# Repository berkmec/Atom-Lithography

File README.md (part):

# Atom Litografi Makinesi (v7.2)

TRL 1–2 (`M0`) Kavramsal Sistem Tasarımı, İndirgenmiş-Mertebe Çok-Fizikli Fizibilite Çalışması, Gerçek-EDA Doğrulamalı Verilog RTL ve Bulut Süperiletken-QPU Kontrol/Dekoder Kıyaslaması

Doğrudan Artefaktlar: [**180/180 Parça Mühendislik Planı (`hardware/DESIGN_BLUEPRINT_180_SUMMARY.md`)**](hardware/DESIGN_BLUEPRINT_180_SUMMARY.md) · [**164-Parça Ana Montaj Paftası (`hardware/cad_parts/master_164_assembly_views.png`)**](hardware/cad_parts/master_164_assembly_views.png) · [Makine-Kontrol RTL (`rtl/machine_ctrl/README.md`)](rtl/machine_ctrl/README.md) · [Etkileşimli HTML5 Model Gezgini (`docs/digital_twin_interactive.html`)](docs/digital_twin_interactive.html) · [BOED Verilog RTL (`rtl/boed_fpga/README.md`)](rtl/boed_fpga/README.md) · [Ana Tasarım (`DESIGN.md`)](research/atom_lithography_machine/DESIGN.md) · [Teknik El Kitabı (`TECHNICAL_MANUAL.md`)](research/atom_lithography_machine/TECHNICAL_MANUAL.md)

---

## Özet

Atom Litografi Makinesi (`v7.2`), zenginleştirilmiş `²⁸Si` üzerinde deterministik tek-atom donör yerleşimi ve hata-toleranslı ölçekleme için geliştirilmiş **`TRL 1–2` (`M0/M1 DESIGN_ONLY`) düzeyinde kavramsal bir sistem mimarisi ve indirgenmiş-mertebe çok-fizikli fizibilite çalışmasıdır**. Depo, `28` ön-kayıtlı sayısal çalışmayı (`Exp124`–`Exp151`), konak makinede gerçek açık-kaynak EDA araçlarıyla (`iverilog 14.0`, `verilator 5.055`, `yosys 0.71+101`, `nextpnr-ecp5` vekili; `no_external_eda_sim = false`, `no_vendor_vivado_pnr = true`, `no_lab_measurement_rtl = true`) doğrulanmış sentezlenebilir IEEE 1364-2005 `Q16.16` BOED-FPGA ve makine-kontrol Verilog RTL modüllerini (`rtl/boed_fpga/`, `rtl/machine_ctrl/`, `rtl/cryo_crossbar_4k/`), gerçek `1% ²⁹Si` elmas-kübik örgü banyosu BOED kıyaslamasını (`results/boed_real_bath_benchmark.json`: `130,4 ms/aday`, `%91,15` doğruluk), fiziksel ODE/PDE/Lindblad/GF(2) tabanlı `auto_recal.py` ve `programmer.py` çözücülerini, `SEMI S2` kılavuzları ve `IEC 61508 SIL-3` mimari hedeflerini referans alan sertifikasız bir `M0` ön emniyet FMEA/HAZOP taramasını (`iec61508_certified = false`, `semi_s2_certified = false`, IEC 61508-6 `PFH` ve `15`-durumlu `λ_DU × β` duyarlılık taraması, `12,0 kWh` LFP UPS `202,8 dk @ %90 DoD`), **tek birleştirilmiş `164` fiziksel katı parçalık su-sızdırmaz 3B CAD ana montajını (`2.957,95 kg`, `0 / 13.366` çakışma, `32/32` kriyo termal, `10/10` GD&T; `10/10` KiCad 8 PCB `1.128/1.128` ağ `0` ERC/`0` DRC + `ngspice-47`)** ve `180` satırlık parametrik `BOM v7.0` (`10-RFQ` taslağı, `no_supplier_quotes = true`, `1.392/1.392` `%100` `SHA-256` sabitli `hardware/parts_registry.json`) paketini birleştirir. Seçili alt-çözücüler mikroskobik veya cebirsel denklemleri doğrudan çözerken sistem düzeyindeki proses, QEC (Stim devre eşiği `%0,60–%0,98`; `Exp147` `FeMoco d=18` ve `RSA-2048 d=24` `p_fail_total = 1,0`, `RSA-2048 d_req = 174,1`), emniyet, maliyet ve kapasite kestirimleri **parametrik/indirgenmiş-mertebe modellere ve literatür varsayımlarına** dayanır. Ayrıca `CellISA v4.0 → OpenQASM 3.0` kontrol derleyicisi, dinamik dekupling, `d=3` tekrar dekoderi ve bit-kesin `Q16.16` BOED algoritmaları `156`-kübitlik süperiletken `ibm_marrakesh` bulut QPU işlemcisinde kontrol/dekoder proxy kıyaslaması olarak çalıştırılmıştır (`Exp145`; silikon fabrikasyonunu doğrulamaz).

## Abstract

Atom Lithography Machine (`v7.2`) is a **`TRL 1–2` (`M0/M1 DESIGN_ONLY`) conceptual systems-architecture and reduced-order multiphysics feasibility study** for deterministic single-atom donor placement in enriched `²⁸Si` and fault-tolerant quantum scaling. The repository combines `28` preregistered numerical studies (`Exp124`–`Exp151`), synthesizable IEEE 1364-2005 `Q16.16` BOED-FPGA and machine-control Verilog RTL verified with real open-source EDA tools on host (`iverilog 14.0`, `verilator 5.055`, `yosys 0.71+101`, `nextpnr-ecp5` proxy; `no_external_eda_sim = false`, `no_vendor_vivado_pnr = true`, `no_lab_measurement_rtl = true`), a real `1% ²⁹Si` diamond-cubic lattice-bath BOED benchmark (`results/boed_real_bath_benchmark.json`: `130.4 ms/cand`, `91.15%` accuracy), physics-based ODE/PDE/Lindblad/GF(2) solvers in `auto_recal.py` and `programmer.py`, an uncertified `M0` preliminary parametric safety FMEA/HAZOP screening (`iec61508_certified = false`, `semi_s2_certified = false`, IEC 61508-6 PFH & `15`-case `λ_DU × β` sweep, upgraded `12.0 kWh` LFP UPS `202.8 min @ 90% DoD`), a **single reconciled `164`-part watertight 3D engineering CAD assembly (`2,957.95 kg`, `0 / 13,366` 3D solid clashes, `32/32` NIST cryo thermal checks, `10/10` GD&T stacks; `10/10` KiCad 8 PCBs `1,128/1,128` nets `0` ERC/`0` DRC + live `ngspice-47`)**, and a parametric `180`-row `BOM v7.0` (`10-RFQ` draft, `no_supplier_quotes = true`, `1,392/1,392` `100%` SHA-256 pinned in `hardware/parts_registry.json`). While selected sub-solvers evaluate microscopic or algebraic physics, system-level process, QEC (honest Stim circuit threshold `0.60–0.98%`; `Exp147` `FeMoco d=18` and `RSA-2048 d=24` yield `p_fail_total = 1.0` under D3 with `RSA-2048 d_req = 174.1`), safety, cost, and throughput estimates rely on **parametric/reduced-order models and literature assumptions**. Separately, the `CellISA v4.0 → OpenQASM 3.0` compiler, dynamical decoupling, `d=3` repetition decoding, and bit-exact `Q16.16` BOED routines were executed on the `156`-qubit superconducting `ibm_marrakesh` cloud QPU as a non-silicon control/decoder proxy (`Exp145`).

---

## Bu Depo Neyi Gösterir, Neyi Kanıtlamaz? (Scope: Demonstrated vs. Not Demonstrated)

| Alan | Gösterilen (Demonstrated) | Kanıtlanmayan (Not Demonstrated) |
|---|---|---|
| Bulut QPU (`Exp145`, `ibm_marrakesh`) | `CellISA v4.0 → OpenQASM 3.0` derleyici, `Echo / XY4`, `d=3` tekrar dekoderi ve `Q16.16` BOED algoritmalarının süperiletken transmon bulut işlemcisinde (`job_id = dc1tdo2nj2vs73dfrfl0`) çalıştırıldığını gösterir. | Silikon `³¹P` implantasyonu, flaş tavlama, MBE, `100 K` IBIC veya herhangi bir atom-litografi donanımını doğrulamaz. |
| Gerçek Açık-Kaynak EDA RTL & ASIC Durumu (`Exp149`, `rtl/boed_fpga/`, `rtl/machine_ctrl/`, `S8.2-02`) | `verilator 5.055 --lint-only -Wall` (`0` uyarı/hata), `iverilog 14.0 + vvp` (`64/64` vektör + `4`-kanal AXI4-Stream `0 LSB`, `584` çevrim, `0` kombinasyonel `/`), `yosys 0.71+101` (`xcup`/`xc7`/`ecp5`) ve `nextpnr-ecp5` (`LFE5U-85F` vekili: `boed_q16_core 43,58 MHz`, `fpga_top_carrier_wrap 79/205 TRELLIS_IO`); `no_external_eda_sim = false`, `real_eda_verified = true`. | Ticari Xilinx Vivado `ZU48DR`/`XC7K325T` P&R zamanlama kapanışı (`no_vendor_vivado_pnr = true`), fiziksel FPGA ölçümü (`no_lab_measurement_rtl = true`) ve SKY130 ASIC tape-out (`tapeout_done = false`, `PRE_FOUNDRY_NCH8_MACRO_PROTOTYPE_NOT_TAPEOUT_READY`, `Exp123 Attempt-2` geçersiz) henüz yapılmamıştır. |
| Yazılım Regresyon Testleri (**`621/621`** çıplak `pytest`, **`50`** takip edilen test dosyası) | Kod tabanının yeniden üretilebilirliğini, birim doğruluğunu, açık-kaynak EDA eş-doğrulamasını ve iç sayısal tutarlılığını gösterir (`35` v7.2 + `14` Stage-2 + `1` `test_qcell_legacy.py` = `50` takip edilen suit; çıplak `pytest -q`: `621 passed, 0 failed`, yeniden koşumda `0` dosya değişimi). | Fiziksel modelin gerçek laboratuvar koşullarında doğru olduğunu kanıtlamaz. |
| Dosya Bütünlüğü (`39/39` v7.2 + `1.392/1.392` Stage-2 `%100` `SHA-256`) | Üretilen artefaktların sonradan değiştirilmediğini doğrulayan dosya-bütünlüğü ve izlenebilirlik özetidir (`hardware/parts_registry.json`, `180/180` boş-olmayan ICD `verification_tests`). | Bilimsel doğrulama, hakemli onay veya endüstriyel sertifikasyon değildir. |
| Fizik, QEC (`Stim`/`Exp147`), `1% ²⁹Si` Banyo & Maliyet (`Exp124`–`Exp151`) | Atomistik/cebirsel hesabı (`sp³d⁵s*` TB, `16B` Lindblad + Gillespie-OU, `45.214` konumlu `1% ²⁹Si` banyo [`130,4 ms/aday`], Stim devre eşiği `%0,60–%0,98`, GF(2) BP-OSD, doğrusal-olmayan Si PDE, UHV ODE) sistem düzeyinde parametrik analizle birleştirir; tüm ön-kayıtlı `FAIL` ve fiziksel duvarları (`Exp147` `UQ4/UQ5/UQ6 FAIL`: `FeMoco d=18` & `RSA-2048 d=24` `p_fail_total = 1,0`, `RSA-2048 d_req = 174,1`; `CPU ldpc BP+OSD-2 34,7–181,7 ms`, sıfır QEC dekoder RTL; `2 kHz` Fourier duvarı; `SNR ≤ 3` uçurumu; `%61,51` step-and-stitch) korur. | Uçtan uca deneysel fiziksel doğrulama veya tedarikçi teklifi değildir (`no_lab_measurement = true`, `no_supplier_quotes = true`, `tapeout_done = false`). |
| Emniyet Analizi (`Exp150`, `PRELIMINARY_PARAMETRIC_CALCULATION_NOT_CERTIFIED`) | `25` satırlı ön `M0` tehlike taraması (`FMEA`), `10` düğümlü `HAZOP`, IEC 61508-6 `PFH` & `15`-durumlu `1oo2D` `λ_DU × β` duyarlılık taraması, RK4 oda ODH geçişi (`60 m³ 0 ACH = %20,57`; havalandırmasız `≤15 m³` oda `%19,47 < %19,5` yasak), yükseltilmiş `12,0 kWh` LFP UPS (`202,8 dk @ %90 DoD ≥ 180 dk`) ve `≥150–200 °C` UHV fırınlama zorunluluğudur. | Sertifikasyon değildir (`iec61508_certified = false`, `semi_s2_certified = false`, `requires_third_party_assessment = true`); SEMI kendi S2 kılavuzu için sertifika vermez, IEC 61508 SIL-3 ise tedarikçi FMEDA verisi, tam emniyet yaşam döngüsü ve bağımsız fonksiyonel emniyet değerlendirmesi gerektirir. |
| Birleşik 3B CAD (`164` fiziksel katı, `2.957,95 kg`, `0/13.366` çakışma) & `10/10` PCB (`0` ERC/`0` DRC) | `164/164` su-sızdırmaz STL/STEP/DXF/SVG (`757.196` üçgen, `32/32` NIST kriyo termal, `10/10` GD&T, `32/32` açık görüş hattı) ve `10/10` tam rotalı KiCad 8 PCB (`1.128/1.128` ağ, `0` ERC/`0` DRC + canlı `ngspice-47`) tasarım doğrulamasıdır (`180` BOM satırı). | Fiziksel üretim/laboratuvar doğrulaması veya tam 3B EM/FEM PCB/kavite son-onayı değildir (`OBS-074`: `ngspice`/analitik doğrulama 3B DOLFINx/openEMS/Palace parazitik/kavite analizinin yerini almaz; `no_lab_measurement = true`). |
| Simülasyonda `FAIL → PASS` İterasyonları (`Exp139`, `Exp141`, `Exp148`) | Kendi model uzayında yapılan tasarım ve parametre iterasyonlarını belgeler (`1440 K → 1530,1 K`, `W2/W3` SOI, `¹²¹Sb` `Q-Echo-8`). | Deneysel fiziksel engel giderimi veya laboratuvar doğrulaması değildir. |
| Üretim Kapasitesi ve `MachineConfig` (Koşullu Üst-Sınır vs. Düşürülmüş Gerçek Banyo) | `2,95×10⁹` atış/gün yalnızca varsayılan `MachineConfig` girdileri altındaki koşullu yazma üst-sınırıdır; gerçek `%1 ²⁹Si` banyo BOED `130,4 ms/aday` (`Exp132` `41,0 ms`'nin `3,18×` yavaşı) ve `%5` ölü blanker kanalında step-and-stitch verimi **`%61,51`**'e düşer. | Fiziksel bir makinede ölçülmüş üretim hızı (throughput) değildir. |

> [!NOTE]
> **Ön-Kayıtlı Hükümler:** Tüm deneylerde başarı ölçütleri hesaplamadan önce `predictions_exp*.json` dosyalarına kaydedilmiştir. Karşılanmayan tüm `FAIL` hükümleri (`Exp124, 126, 127, 128 [v7 Full], 129, 131, 134, 136, 137, 138 [FT3/FT5], 139, 142, 143 [DH1–DH5], 144 [QL4], 147 [UQ2, UQ4, UQ5, UQ6], 148 [SQ4]`) gizlenmeden ve kök-nedeniyle raporlanmıştır.

---

## Genel Görünüm

### 164-Parça Bütünleşik Mühendislik Ana Montaj Paftası (`v8.0-blueprint`, `2.957,95 kg`, `0 / 13.366` 3B Çakışma, `M0/M1 DESIGN_ONLY`)

> **180 / 180 Parça Mühendislik Planı (`hardware/parts_registry.json`, `M0/M1_DESIGN_ONLY`):** `164/164` su-sızdırmaz 6-formatlı CAD (`.stl`, ISO 10303-21 `.step`, `.dxf`, `librsvg` doğrulamalı GD&T `.svg`, `.scad`, `.json`; `757.196` üçgen, `0/13.366` küresel çakışma, **`2.957,9454 kg`** tek birleştirilmiş kütle, `32/32` NIST kriyo termal, `10/10` GD&T) · `%100` pad'den pad'e fiziksel rotalı `10/10` KiCad 8 PCB (`1.128/1.128` ağ, `12.883` segment, `3.495` via, `0` ERC/DRC/HV) + `10/10` canlı `ngspice-47` + `95/95` elektrik ICD (`12,0 kWh` LFP UPS `202,8 dk @ %90 DoD`) · `1.392/1.392` (`%100`) `SHA-256` sabitli + `180/180` boş-olmayan ICD `verification_tests` · `7` makine-kontrol Verilog RTL modülü (`3.212` LOC, `Verilator 0` uyarı, `Icarus 6/6`, `Yosys xcup/xc7/ecp5`, `nextpnr-ecp5` vekili) · `S8.4-02` SCADA & `S8.2-02` dürüst OpenROAD manifestosu (`PRE_FOUNDRY_NCH8_MACRO_PROTOTYPE_NOT_TAPEOUT_READY`). Detay: [`hardware/DESIGN_BLUEPRINT_180_SUMMARY.md`](hardware/DESIGN_BLUEPRINT_180_SUMMARY.md).

### Kavramsal Sistem Özet Panosu (`v7.2`)

| Tarihsel `v6.0` Şematik Önizleme (Arşiv) | Tarihsel `v6.0` Kesit (Arşiv) | Tarihsel `v6.0` Patlatılmış Görünüm (Arşiv) |
|---|---|---|
|  |  |  |

---

## 1. Sistem Özeti ve Başlıca Model Parametreleri (`v7.2`, `TRL 1–2 / M0`)

| Parametre | Model Çıktısı / Tasarım Hedefi | Kaynak / Deney |
|---|---|---|
| Yerleştirme belirsizliği (`5 keV ³¹P⁺`, `Arch-B`) | İndirgenmiş model `σ_tot = 3,59–3,63 nm`; gerçek sonsuz-alan ZBL/`iradina` 3B BCA `σ_lat = 4,39–4,44 nm` (`σ_tot = 4,76 nm > 3,80 nm`, dürüst fizik duvarı `OBS-039`) | `Exp124`, `Exp139` |
| Titreşim ve işaret kararlılığı (`S6.9 CFG4`) | `σ_stage = 0,102 nm`, `σ_pointing = 0,147 nm`; `S4.3-01` EDM fleksür CalculiX C3D10 `k_eff = 1,97–2,02 MN/m`, `13/13` açık optik LOS | `Exp133`, `s4_stage_metrology.py` |
| Flaş tavlama ve epitaksiyel kapsülleme (`S5.5`, `S5.6`) | `1530,1 K` / `1,0 ms`, `8 nm` LT-MBE, `S_ε = 0,390 µeV/√Hz`; `≥150–200 °C` UHV fırınlama zorunlu (fırınlamasız stres gaz salınımı `1,12×10⁻⁸ mbar`) | `Exp130`, `Exp139`, `OBS-124` |
| Paralel yazma ve tek-kriyostat kapasitesi | `32×32 = 1.024` demetçik; koşullu yazma üst-sınırı `2,95×10⁹` atış/gün (`%5` ölü kanalda dürüst step-and-stitch verimi **`%61,51`**; gerçek `%1 ²⁹Si` banyo BOED `130,4 ms/aday`) | `Exp124`, `Exp140`, `auto_recal.py` |
| Gerçek `1% ²⁹Si` örgü banyosu BOED (`N = 260`) | `%91,15` vs `%84,62` Uniform (`130,4 ms/aday`, `10,46×` prob / `26,29×` zaman hızlanması, `A_par RMSE = 96,17 Hz`, eski `Exp132` `%100` FNR; dürüst `2 kHz` Fourier duvarı & `SNR ≤ 3` uçurumu) | `boed_real_bath_benchmark.json` |
| `M4` iki-kübit kapı & QEC eşik gerçekliği | Gerçek Stim yüzey-kodu devre eşiği **`%0,60–%0,98`** (eski tur-başı `%1,60` değil); sentetik sıkıştırmasız 4×4 Tosi + Route C üst-eşikte (`Exp137`/`143` `HORIZON_TARGET_REQUIRED`); Option-HPC C++ `ldpc` `BP+OSD-2` `34,7–181,7 ms` (sıfır QEC dekoder RTL) | `Exp137`, `Exp138`, `Exp143`, `programmer.py` |
| `qLDPC` bellek (`[[144,12,12]]` Gross Code) | Cebir doğrulandı; düzlem-katlı yerleşimde `10.372` hava köprüsü ve `%26,4` `>300 µm` Manhattan aşımı (dürüst `QL4 FAIL` / Faz-3 Ar-Ge) | `Exp144` |
| Evrensel `qLDPC` (`[[288,12,18]]`) ve Algoritma Ufku | **`Exp147` dürüst `UQ2/UQ4/UQ5/UQ6 FAIL` (`3/7 PASS`)**: D3 altında `FeMoco d=18` ve `RSA-2048 d=24` ikisi de **`p_fail_total = 1,0`** (`RSA-2048 d_req = 174,1`); `16` / `291` kriyostat sayıları yalnızca `p_2q ≤ %0,15–%0,20` ve `p_meas ≤ %0,15` gerektiren ayak-izi alt-sınırlarıdır | `Exp147` |
| `¹²¹Sb` (`I=7/2`) kudit koruma ve `SU(8)` kontrol | `Q-Echo-8` statik `0,5800 → 0,99908` (`455,5×` hata azalması); `SU(8)` `≥ 0,9954`; `1/f` `Q-Echo-64` `28,08×` (`1,45 ms`); `B_M4 = 0,1785 T` spin karışımı dürüst sınır | `Exp148` |
| Gerçek-EDA doğrulamalı Verilog RTL & OpenROAD | `rtl/boed_fpga/` (`0` `/` bölücü, `verilator 5.055 -Wall` `0` uyarı, `iverilog` `64/64` `0 LSB` / `584` çevrim, `yosys` `xcup_top16` `102.886` LUT / `1.584` DSP) + `rtl/machine_ctrl/` (`3.212` LOC, `nextpnr-ecp5` vekili `boed_q16_core 43,58 MHz`, `fpga_top_carrier_wrap 79/205 TRELLIS_IO`; `no_vendor_vivado_pnr = true`) · SKY130 `S8.2-02` `PRE_FOUNDRY_NCH8_MACRO_PROTOTYPE_NOT_TAPEOUT_READY` (`tapeout_done = false`) | `Exp149`, `rtl_machine_ctrl_audit.json`, `openroad_signoff_manifest.json` |
| Ön emniyet taraması (sertifikasız `M0` parametrik hesap) | `iec61508_certified = false`, `semi_s2_certified = false`, `25` FMEA `max RPN 280 → 42`, IEC 61508-6 `PFH` & `15`-durumlu `λ_DU × β` taraması, RK4 ODH (`60 m³ 0 ACH = %20,57`; havalandırmasız `≤15 m³` oda `%19,47 < %19,5` yasak), **`12,0 kWh` LFP UPS `202,8 dk @ %90 DoD`** (`≥ 180 dk` PASS; `12,5 kW` PT420 şebeke tarafında), `S7.SAFETY $145k` | `Exp150`, `master_electrical_power_ups_budget.json` |
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
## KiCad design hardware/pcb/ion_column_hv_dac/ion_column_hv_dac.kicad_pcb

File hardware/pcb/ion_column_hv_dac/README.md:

# Ion Column 20-Bit HV DAC, 5 kV 1000:1 Divider, 3-Stage Active Ripple Filter & `< 5 µs` Trim PCB

**BOM Coverage:** `S1.3-03`, `S2.3-04`, `S6.10-04` (interfacing `S1.1-05`, `S1.2-03`, `S1.5-03`, `S4.5-03` and `rtl/machine_ctrl/spi_dac_hv_ctrl.v`)  
**Epistemic Status:** `M0/M1_DESIGN_ONLY` — `no_lab_measurement=true`, `no_physical_fab=true`, `iec61508_certified=false`, `semi_s2_certified=false`. All active semiconductors are `{Aday-COTS}` candidate parts.

## 1. Board Summary & Strict KiCad 8 EDA Verification

| Parameter | Value / Measured Result | Requirement / Spec | Status |
| :--- | :--- | :--- | :---: |
| Stackup & Geometry | 4-layer Isola FR408HR (`ε_r=3.66`, CTI `≥ 600` MG-I), `220 × 150 mm`, `1.67 mm` thick | 4L HV PCB (`≥ 12 mm` @ `5 kV`) | **PASS** |
| Physical Routing & Connectivity | **`72 / 72` multi-pin nets routed (`100%`)**, `1,104` segments, `269` vias, **`0` unrouted**, **`0` unconnected**, **`0` dangling** | 100% pad-to-pad routed Union-Find DRC | **PASS** |
| Schematic / PCB Netlist | `102` components, `72` nets, `2` milled `Edge.Cuts` air-slots (L-shaped `5 kV` barrier) | Strict S-expr + SCH↔PCB parity | **PASS** |
| ERC / DRC Errors | **`0` ERC / `0` DRC** | `0 / 0` | **PASS** |
| `5 kV` HV Clearance / Creepage (`HV_5KV_*`) | **`14.020 mm`** air clearance, **`31.580 mm`** surface creepage around milled air-slots, `through_board_ok=true` | `≥ 12.0 mm` clr / `≥ 16.0 mm` crp (IEC 61010-1 / IPC-2221B) | **PASS** |
| Controlled-Impedance `50 Ω` Coax I/O (`12` checks) | `Z0 = 50.00 Ω` (`0.001%` max error on `F.Cu`) | `50 Ω ± 5%` | **PASS** |

## 2. Architecture

- **HV Isolation Bay (`x = 10..84 mm`, `y = 14..56 mm`):** `5 kV` alumina-standoff turrets (`S1.1-05` in; `S1.3-03` landing, `S2.3-04` mini-lens, `S1.2-03` Wien, `S1.5-03` HDA outputs), 3-stage `10 kΩ / 10 nF` (`5 kV` Ohmite MOX + `6 kV` WIMA FKP1) RC ripple filter with closed-loop `ADA4898-1` anti-phase ripple cancellation, plus hard-wired `HV_SAFE_CLAMP` (`Gigavac G81C` `10 kV` NC vacuum relay + `Ohmite MOX-4 500 kΩ` dump resistor + `IXTH1N450HV` `4.5 kV` MOSFET backup).
- **Milled `Edge.Cuts` Air-Slots:** L-shaped HV barrier enclosing the `5 kV` top-left bay (`x ≤ 86 mm, y ≤ 54 mm`): vertical `4.0 × 74.0 mm` slot (`x = 96..100 mm, y = 8..82 mm`) straddled by the `36 mm`-pitch `Caddock USF370` `99.900 MΩ` precision divider resistor & `2.0 pF` compensation cap, paired with horizontal `80.0 × 4.0 mm` slot (`y = 68..72 mm`) isolating `5 kV` hot nodes from `HV_RTN` / LV clamp coils while providing a clean LV routing corridor below `y = 86 mm`.
- **20-Bit Ultra-Low-Noise DAC & Trim Bay (`x = 114..216 mm`):** `ADuM1401` isolated `spi_dac_hv_ctrl.v` SPI/LDAC/CLR/CLAMP interface, `4× AD5791BRUZ` 20-bit DACs with `LT6655B-5` + `OPA211` `±10 V` reference, `Vishay Z201 100.00 kΩ` `1000:1` low-side divider + `ADA4522-1`/`OPA211` HV servo error integrator, `THS4031` fast `< 5 µs` on-the-fly interferometer deflector trim summer (`S4.5-03`), and `LT3045/LT3094/ADP7142` ultra-low-noise LDO tree.

## 3. Live `ngspice-47` & Independent MNA Results (`ion_hv_filter_trim.cir`)

| Metric | `ngspice-47` Measured | Independent Python MNA Ref | Target / Spec | Status |
| :--- | :---: | :---: | :---: | :---: |
| `100 kHz` Active 3-Stage HV Ripple Rejection | **`-125.814 dB`** (`+17.91 dB` active boost) | Passive `-107.907 dB` vs MNA `-107.9086 dB` (`0.0016 dB` diff) | `> 80 dB` (`< -80 dB`) | **PASS** |
| Output Ripple for `10 Vpp @ 100 kHz` on `5.000 kV` | **`0.147 mVpp`** (`t = 1.52–1.60 ms`) | Asymptotic steady-state `5.12 µVpp` | `< 1 mVpp` (`< 2 mVpp` `S2.3-04`) | **PASS** |
| Precision `1000:1` Caddock HV Feedback Divider | `5000.000 V → 4.999995 V` (ratio **`1000.001`**, `1.0 ppm` err) | MNA `1000.000` | `≤ 100 ppm` (`dE/E ≤ 1e-4`) | **PASS** |
| Fast Deflector Trim Summer Step (`S4.5-03`) | `10–90%` rise **`0.732 µs`**, `1%` settle **`1.561 µs`** | — | `< 5.0 µs` | **PASS** |
| M4 20-Bit Dipole Gate DAC Spot Noise (`S6.10-04`) | **`8.587 nV/√Hz`** `@ 1.0 kHz` (`1.735 µVrms` `10 Hz–1 MHz`) | — | `< 500 nV/√Hz` (`< 0.5 µV/√Hz`) | **PASS** |

## 4. Reproducibility

```bash
PYTHONPATH=.:src python -B hardware/pcb/ion_column_hv_dac/build_ion_column_hv_dac.py
PYTHONPATH=.:src pytest tests/test_pcb_hv_laser_safety.py -v -p no:cacheprovider
```

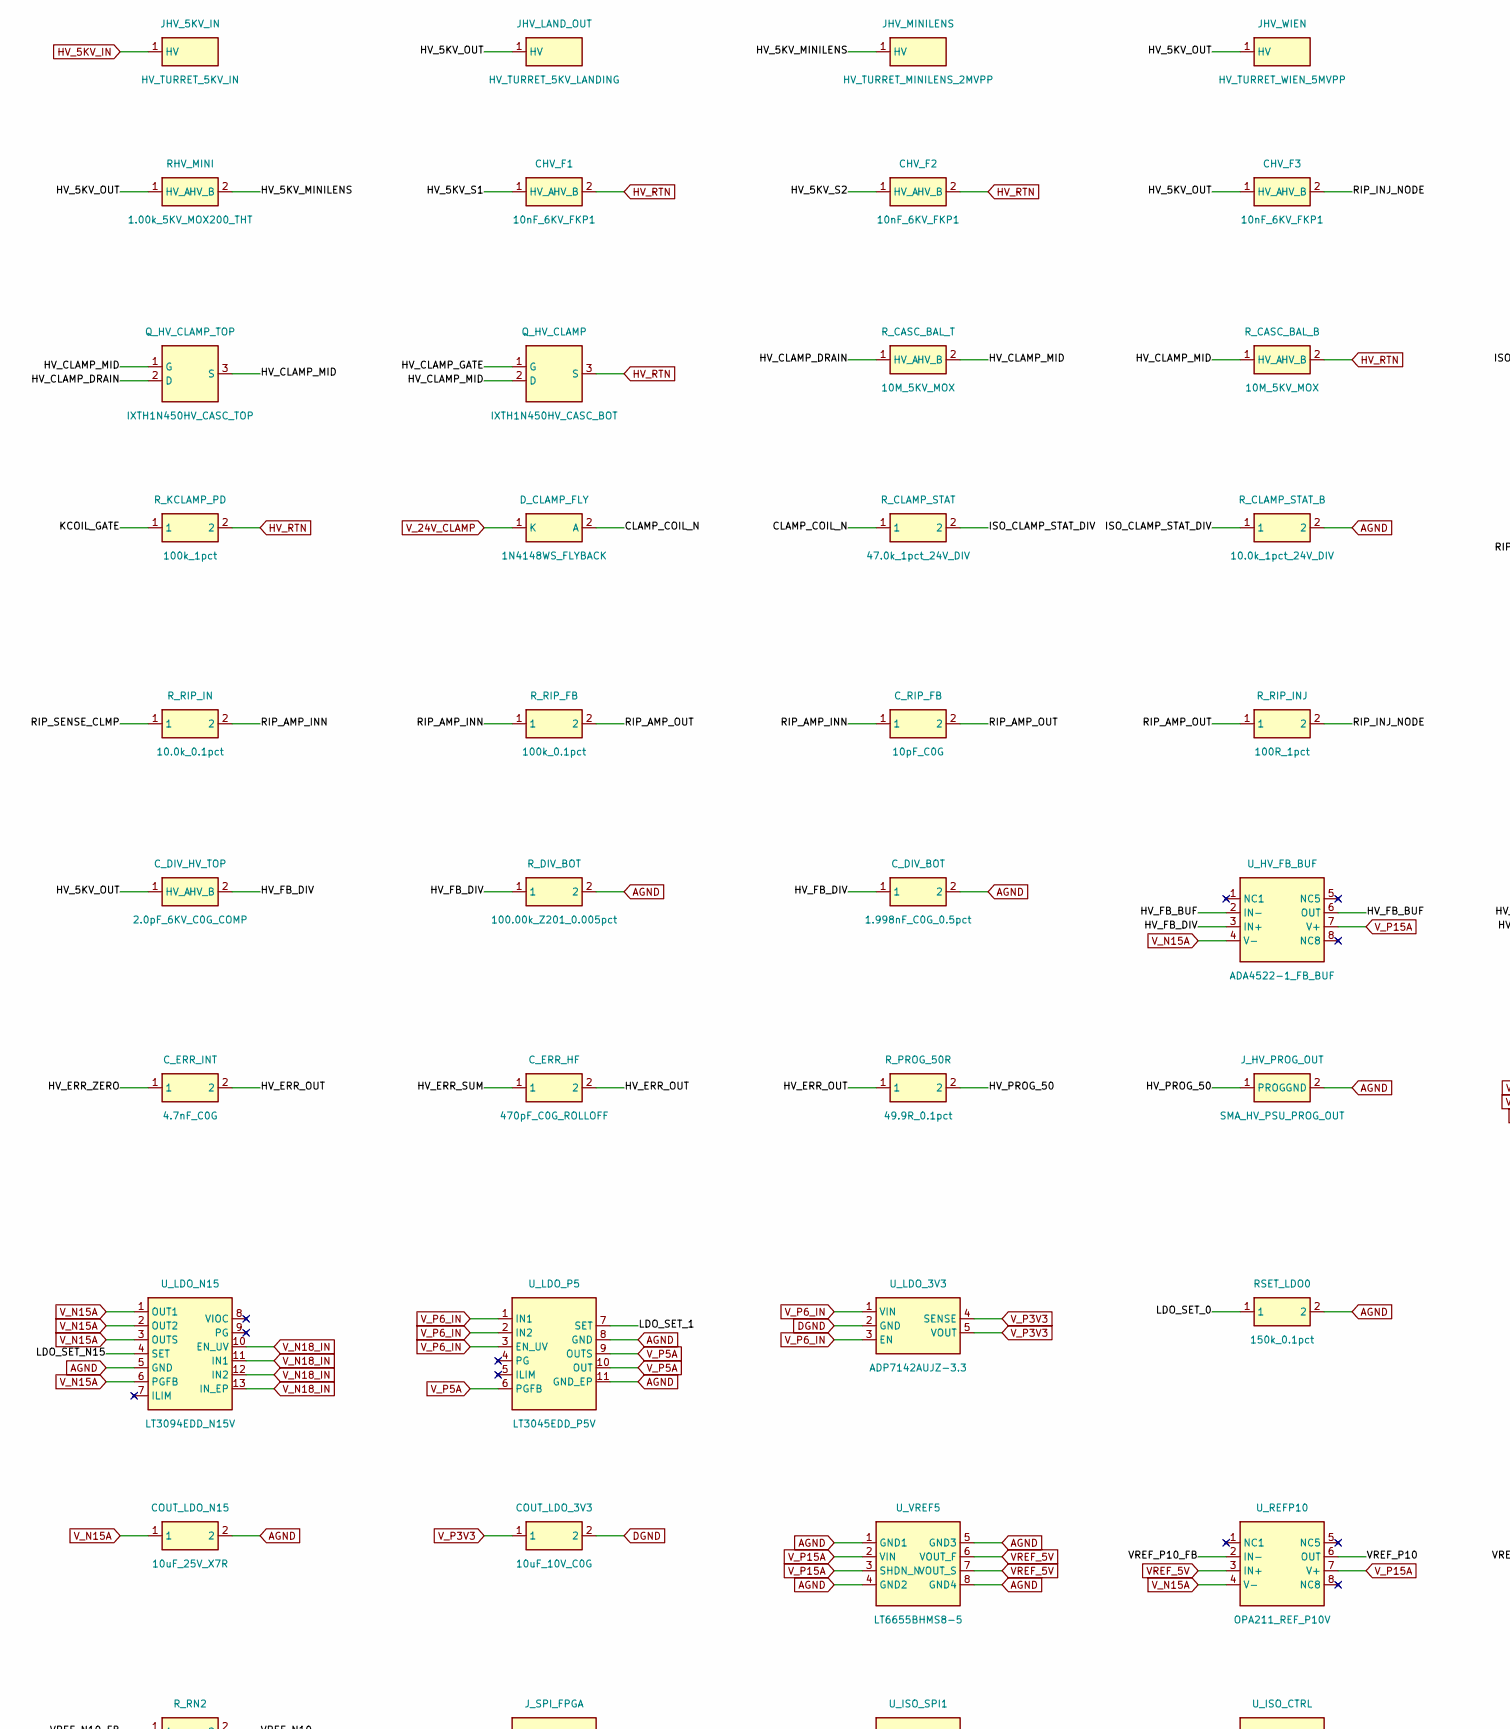
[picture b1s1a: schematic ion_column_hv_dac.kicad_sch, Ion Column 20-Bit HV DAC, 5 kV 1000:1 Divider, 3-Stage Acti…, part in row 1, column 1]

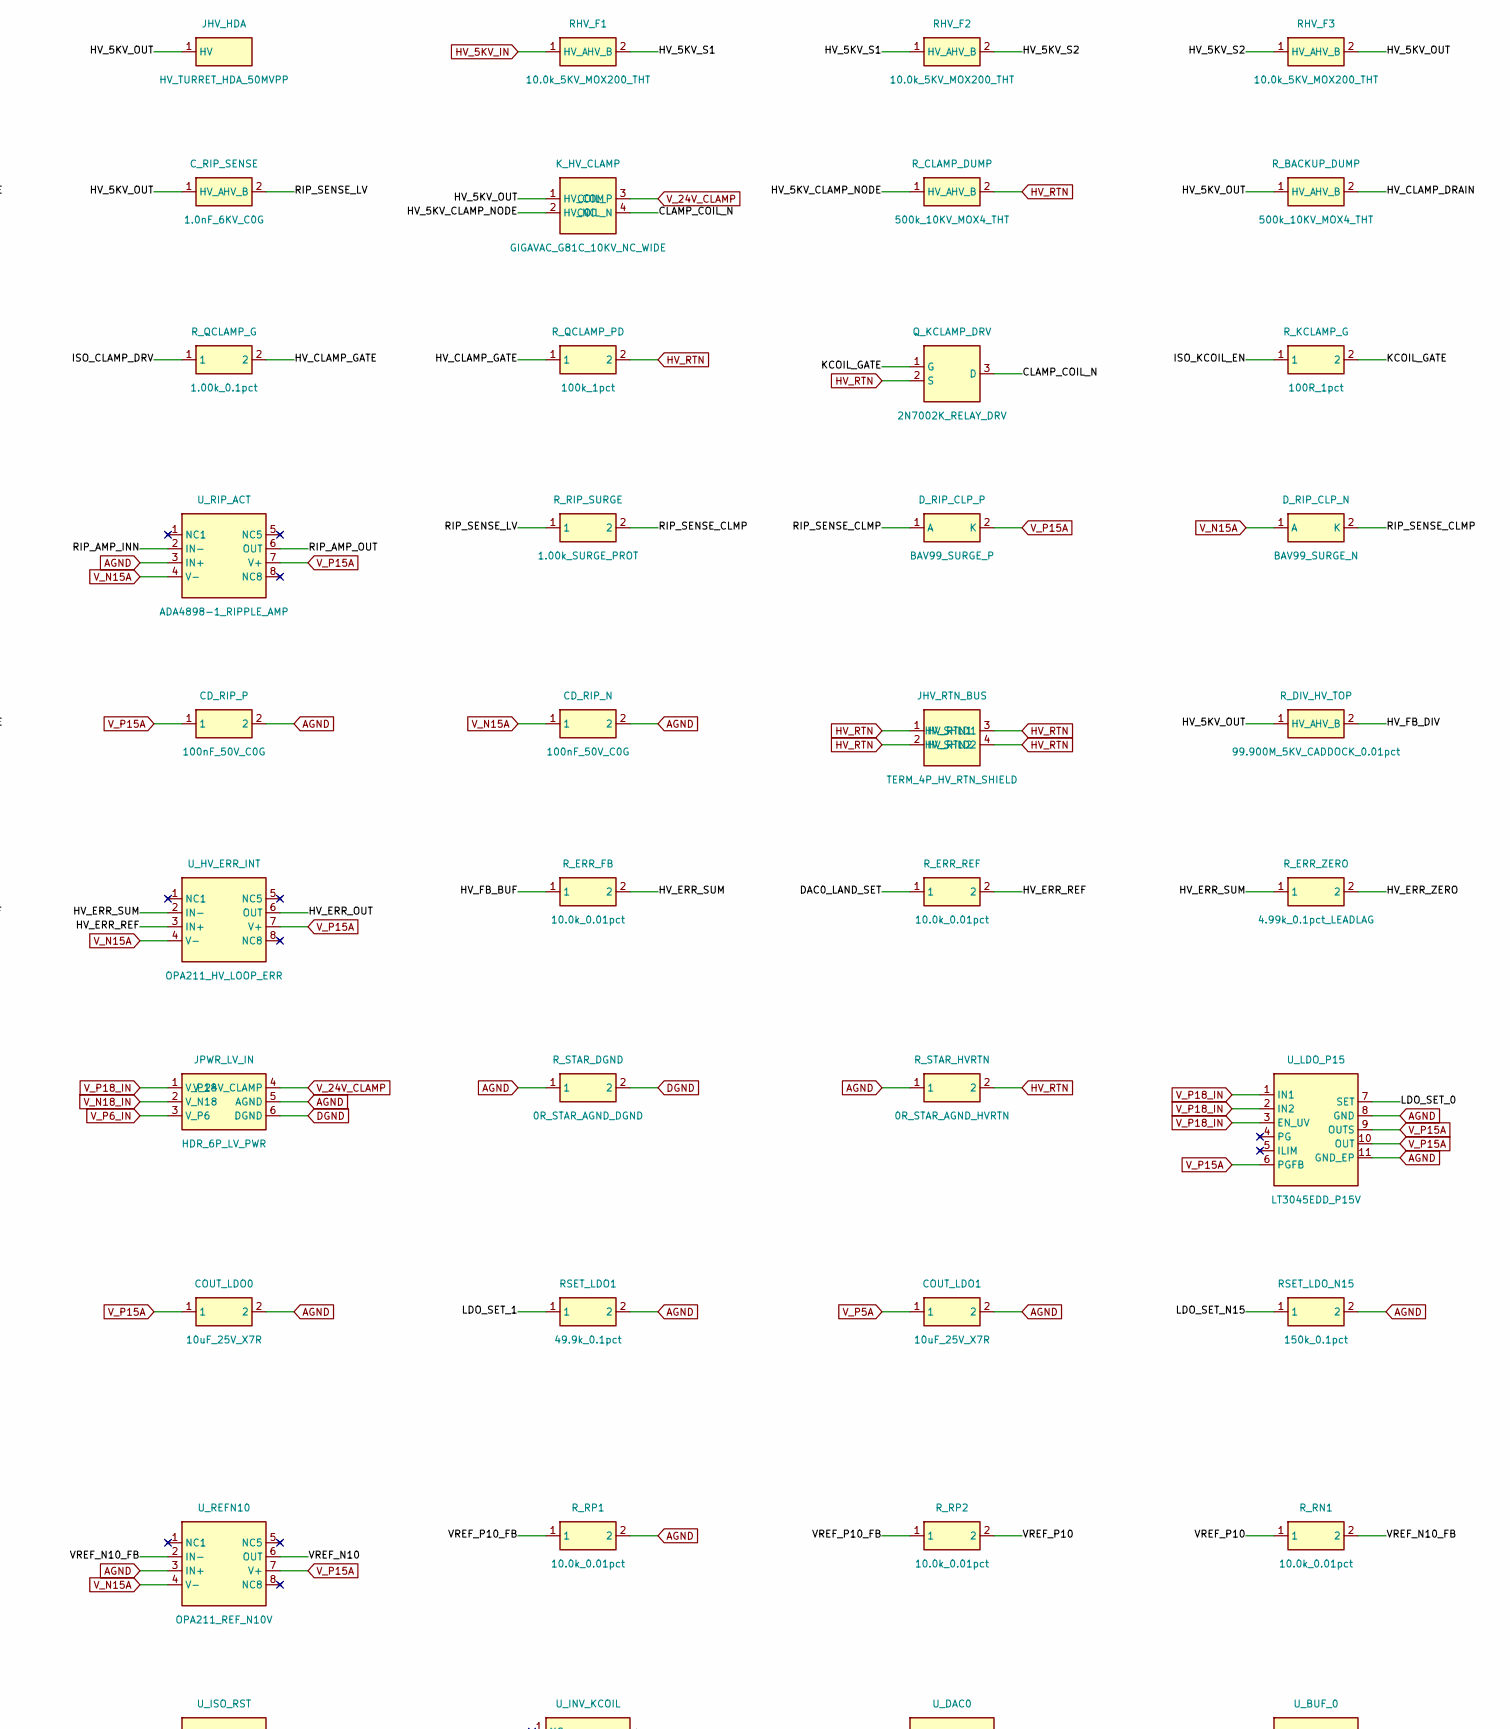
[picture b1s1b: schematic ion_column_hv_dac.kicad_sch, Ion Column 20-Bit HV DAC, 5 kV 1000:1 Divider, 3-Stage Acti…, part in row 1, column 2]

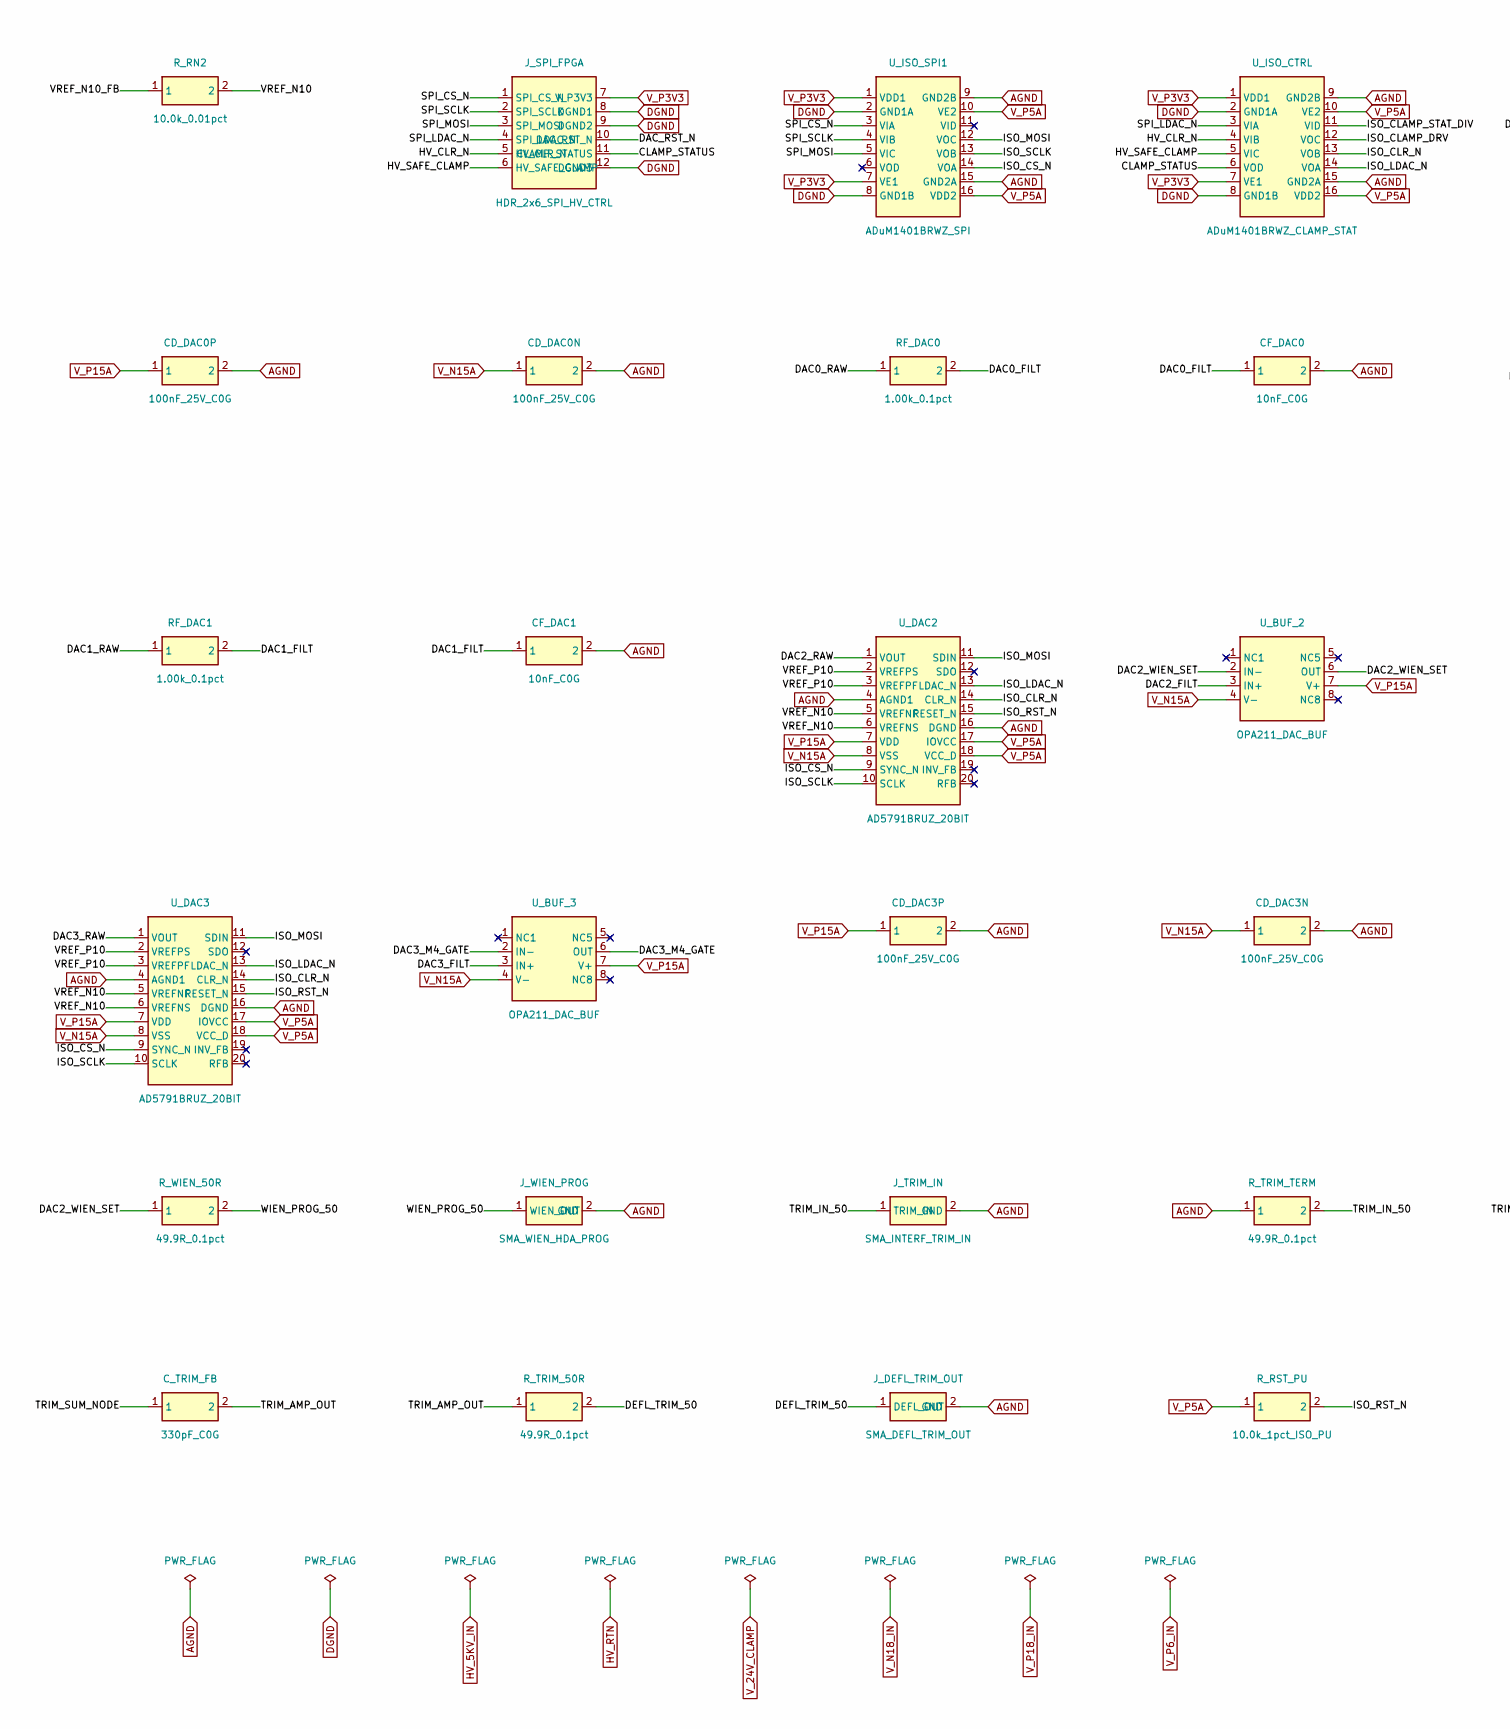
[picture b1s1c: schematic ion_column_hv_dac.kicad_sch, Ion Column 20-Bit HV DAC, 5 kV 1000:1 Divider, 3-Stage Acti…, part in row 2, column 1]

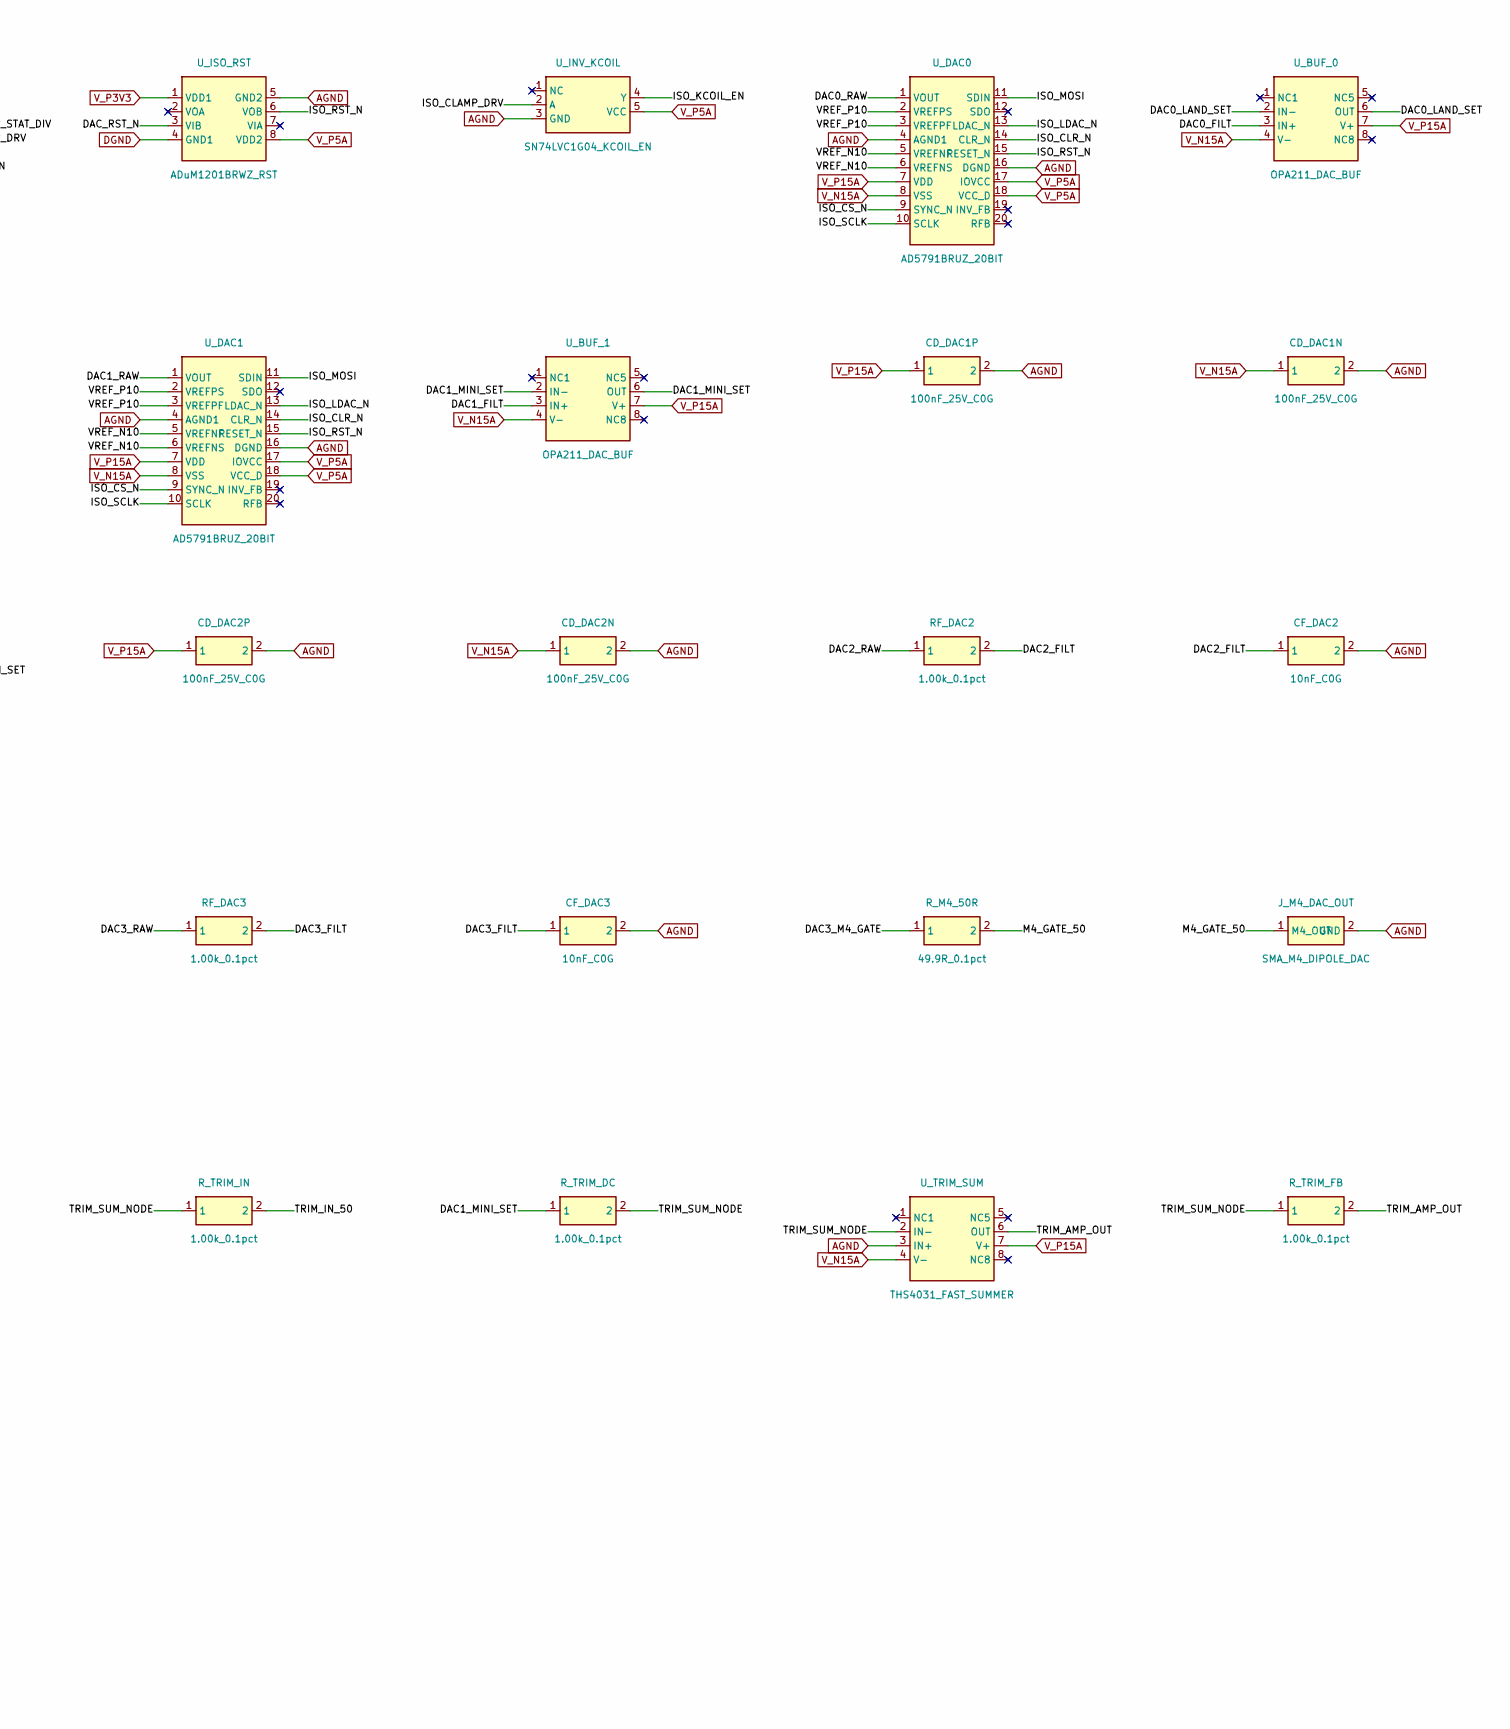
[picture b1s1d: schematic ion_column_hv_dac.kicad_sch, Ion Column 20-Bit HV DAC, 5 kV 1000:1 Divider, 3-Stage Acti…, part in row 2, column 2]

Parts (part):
CD_DAC0N, CD_DAC0P, CD_DAC1N, CD_DAC1P, CD_DAC2N, CD_DAC2P, CD_DAC3N, CD_DAC3P: 100nF_25V_C0G; C_0603_1608Metric; MPN 100nF_25V_C0G
CD_RIP_N: 100nF_50V_C0G; C_0805_2012Metric; MPN 100nF_50V_C0G
CD_RIP_P: 100nF_50V_C0G; C_0805_2012Metric; MPN 100nF_50V_C0G
CF_DAC0, CF_DAC1, CF_DAC2, CF_DAC3: 10nF_C0G; C_0603_1608Metric; MPN 10nF_C0G
CHV_F1, CHV_F2, CHV_F3: 10nF_6KV_FKP1; WIMA_FKP1_6KV_P34mm; MPN WIMA_FKP1Y021007D
COUT_LDO0, COUT_LDO1: 10uF_25V_X7R; C_0805_2012Metric; MPN 10uF_25V_X7R
COUT_LDO_3V3: 10uF_10V_C0G; C_0805_2012Metric; MPN 10uF_10V_C0G
COUT_LDO_N15: 10uF_25V_X7R; C_0805_2012Metric; MPN 10uF_25V_X7R
C_DIV_BOT: 1.998nF_C0G_0.5pct; C_0805_2012Metric; MPN 1.998nF_C0G_0.5pct
C_DIV_HV_TOP: 2.0pF_6KV_C0G_COMP; HV_CAP_6KV_P36mm; MPN Knowles_2225J6K002P0C
C_ERR_HF: 470pF_C0G_ROLLOFF; C_0805_2012Metric; MPN 470pF_C0G_ROLLOFF
C_ERR_INT: 4.7nF_C0G; C_0805_2012Metric; MPN 4.7nF_C0G
C_RIP_FB: 10pF_C0G; C_0805_2012Metric; MPN 10pF_C0G
C_RIP_SENSE: 1.0nF_6KV_C0G; WIMA_FKP1_6KV_P34mm; MPN Vishay_HV_102K6KV
C_TRIM_FB: 330pF_C0G; C_0603_1608Metric; MPN 330pF_C0G
D_CLAMP_FLY: 1N4148WS_FLYBACK; D_0805_2012Metric; MPN 1N4148WS_FLYBACK
D_RIP_CLP_N: BAV99_SURGE_N; D_0805_2012Metric; MPN BAV99_SURGE_N
D_RIP_CLP_P: BAV99_SURGE_P; D_0805_2012Metric; MPN BAV99_SURGE_P
JHV_5KV_IN: HV_TURRET_5KV_IN; HV_ALUMINA_TURRET_5KV; MPN Keystone_1502_Alumina_5kV
JHV_HDA: HV_TURRET_HDA_50MVPP; HV_ALUMINA_TURRET_5KV; MPN Keystone_1502_Alumina_5kV
JHV_LAND_OUT: HV_TURRET_5KV_LANDING; HV_ALUMINA_TURRET_5KV; MPN Keystone_1502_Alumina_5kV
JHV_MINILENS: HV_TURRET_MINILENS_2MVPP; HV_ALUMINA_TURRET_5KV; MPN Keystone_1502_Alumina_5kV
JHV_RTN_BUS: TERM_4P_HV_RTN_SHIELD; HDR_1x4_5.08mm; MPN TERM_4P_HV_RTN_SHIELD
JHV_WIEN: HV_TURRET_WIEN_5MVPP; HV_ALUMINA_TURRET_5KV; MPN Keystone_1502_Alumina_5kV
JPWR_LV_IN: HDR_6P_LV_PWR; HDR_1x6_2.54mm; MPN HDR_6P_LV_PWR
J_DEFL_TRIM_OUT: SMA_DEFL_TRIM_OUT; SMA_EdgeMount; MPN SMA_DEFL_TRIM_OUT
J_HV_PROG_OUT: SMA_HV_PSU_PROG_OUT; SMA_EdgeMount; MPN SMA_HV_PSU_PROG_OUT
J_M4_DAC_OUT: SMA_M4_DIPOLE_DAC; SMA_EdgeMount; MPN SMA_M4_DIPOLE_DAC
J_SPI_FPGA: HDR_2x6_SPI_HV_CTRL; HDR_2x6_2.54mm; MPN HDR_2x6_SPI_HV_CTRL
J_TRIM_IN: SMA_INTERF_TRIM_IN; SMA_EdgeMount; MPN SMA_INTERF_TRIM_IN
J_WIEN_PROG: SMA_WIEN_HDA_PROG; SMA_EdgeMount; MPN SMA_WIEN_HDA_PROG
K_HV_CLAMP: GIGAVAC_G81C_10KV_NC_WIDE; HV_VACUUM_RELAY_G81C_W18_P36mm; MPN Gigavac_G81C245
Q_HV_CLAMP: IXTH1N450HV_CASC_BOT; TO-247-3_Vertical; MPN IXYS_IXTH1N450HV
Q_HV_CLAMP_TOP: IXTH1N450HV_CASC_TOP; TO-247-3_Vertical; MPN IXYS_IXTH1N450HV
Q_KCLAMP_DRV: 2N7002K_RELAY_DRV; SOT-23; MPN 2N7002K
RF_DAC0, RF_DAC1, RF_DAC2, RF_DAC3: 1.00k_0.1pct; R_0603_1608Metric; MPN 1.00k_0.1pct
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
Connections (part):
AGND: CD_DAC0N.2, CD_DAC0P.2, CD_DAC1N.2, CD_DAC1P.2, CD_DAC2N.2, CD_DAC2P.2, CD_DAC3N.2, CD_DAC3P.2, CD_RIP_N.2, CD_RIP_P.2, CF_DAC0.2, CF_DAC1.2, CF_DAC2.2, CF_DAC3.2, COUT_LDO0.2, COUT_LDO1.2, COUT_LDO_N15.2, C_DIV_BOT.2, JPWR_LV_IN.5 (AGND), J_DEFL_TRIM_OUT.2 (GND), J_HV_PROG_OUT.2 (GND), J_M4_DAC_OUT.2 (GND), J_TRIM_IN.2 (GND), J_WIEN_PROG.2 (GND), RSET_LDO0.2, RSET_LDO1.2, RSET_LDO_N15.2, R_CLAMP_STAT_B.2, R_DIV_BOT.2, R_RP1.2, R_STAR_DGND.1, R_STAR_HVRTN.1, R_TRIM_TERM.1, U_DAC0.4 (AGND1), U_DAC0.16 (DGND), U_DAC1.4 (AGND1), U_DAC1.16 (DGND), U_DAC2.4 (AGND1), U_DAC2.16 (DGND), U_DAC3.4 (AGND1), U_DAC3.16 (DGND), U_INV_KCOIL.3 (GND), U_ISO_CTRL.9 (GND2B), U_ISO_CTRL.15 (GND2A), U_ISO_RST.5 (GND2), U_ISO_SPI1.9 (GND2B), U_ISO_SPI1.15 (GND2A), U_LDO_N15.5 (GND), U_LDO_P5.8 (GND), U_LDO_P5.11 (GND_EP), U_LDO_P15.8 (GND), U_LDO_P15.11 (GND_EP), U_REFN10.3 (IN+), U_RIP_ACT.3 (IN+), U_TRIM_SUM.3 (IN+), U_VREF5.1 (GND1), U_VREF5.4 (GND2), U_VREF5.5 (GND3), U_VREF5.8 (GND4)
CLAMP_COIL_N: D_CLAMP_FLY.2 (A), K_HV_CLAMP.4 (COIL_N), Q_KCLAMP_DRV.3 (D), R_CLAMP_STAT.1
CLAMP_STATUS: J_SPI_FPGA.11 (CLAMP_STATUS), U_ISO_CTRL.6 (VOD)
DAC0_FILT: CF_DAC0.1, RF_DAC0.2, U_BUF_0.3 (IN+)
DAC0_LAND_SET: R_ERR_REF.1, U_BUF_0.2 (IN-), U_BUF_0.6 (OUT)
DAC0_RAW: RF_DAC0.1, U_DAC0.1 (VOUT)
DAC1_FILT: CF_DAC1.1, RF_DAC1.2, U_BUF_1.3 (IN+)
DAC1_MINI_SET: R_TRIM_DC.1, U_BUF_1.2 (IN-), U_BUF_1.6 (OUT)
DAC1_RAW: RF_DAC1.1, U_DAC1.1 (VOUT)
DAC2_FILT: CF_DAC2.1, RF_DAC2.2, U_BUF_2.3 (IN+)
DAC2_RAW: RF_DAC2.1, U_DAC2.1 (VOUT)
DAC2_WIEN_SET: R_WIEN_50R.1, U_BUF_2.2 (IN-), U_BUF_2.6 (OUT)
DAC3_FILT: CF_DAC3.1, RF_DAC3.2, U_BUF_3.3 (IN+)
DAC3_M4_GATE: R_M4_50R.1, U_BUF_3.2 (IN-), U_BUF_3.6 (OUT)
DAC3_RAW: RF_DAC3.1, U_DAC3.1 (VOUT)
DAC_RST_N: J_SPI_FPGA.10 (DAC_RST_N), U_ISO_RST.3 (VIB)
DEFL_TRIM_50: J_DEFL_TRIM_OUT.1 (DEFL_OUT), R_TRIM_50R.2
DGND: COUT_LDO_3V3.2, JPWR_LV_IN.6 (DGND), J_SPI_FPGA.8 (DGND1), J_SPI_FPGA.9 (DGND2), J_SPI_FPGA.12 (DGND3), R_STAR_DGND.2, U_ISO_CTRL.2 (GND1A), U_ISO_CTRL.8 (GND1B), U_ISO_RST.4 (GND1), U_ISO_SPI1.2 (GND1A), U_ISO_SPI1.8 (GND1B), U_LDO_3V3.2 (GND)
HV_5KV_CLAMP_NODE: K_HV_CLAMP.2 (HV_NC), R_CLAMP_DUMP.1 (HV_A)
HV_5KV_IN: JHV_5KV_IN.1, RHV_F1.1 (HV_A)
HV_5KV_MINILENS: JHV_MINILENS.1, RHV_MINI.2 (HV_B)
HV_5KV_OUT: CHV_F3.1 (HV_A), C_DIV_HV_TOP.1 (HV_A), C_RIP_SENSE.1 (HV_A), JHV_HDA.1, JHV_LAND_OUT.1, JHV_WIEN.1, K_HV_CLAMP.1 (HV_COM), RHV_F3.2 (HV_B), RHV_MINI.1 (HV_A), R_BACKUP_DUMP.1 (HV_A), R_DIV_HV_TOP.1 (HV_A)
HV_5KV_S1: CHV_F1.1 (HV_A), RHV_F1.2 (HV_B), RHV_F2.1 (HV_A)
HV_5KV_S2: CHV_F2.1 (HV_A), RHV_F2.2 (HV_B), RHV_F3.1 (HV_A)
HV_CLAMP_DRAIN: Q_HV_CLAMP_TOP.2 (D), R_BACKUP_DUMP.2 (HV_B), R_CASC_BAL_T.1 (HV_A)
HV_CLAMP_GATE: Q_HV_CLAMP.1 (G), R_QCLAMP_G.2, R_QCLAMP_PD.1
HV_CLAMP_MID: Q_HV_CLAMP.2 (D), Q_HV_CLAMP_TOP.1 (G), Q_HV_CLAMP_TOP.3 (S), R_CASC_BAL_B.1 (HV_A), R_CASC_BAL_T.2 (HV_B)
HV_CLR_N: J_SPI_FPGA.5 (HV_CLR_N), U_ISO_CTRL.4 (VIB)
HV_ERR_OUT: C_ERR_HF.2, C_ERR_INT.2, R_PROG_50R.1, U_HV_ERR_INT.6 (OUT)
HV_ERR_REF: R_ERR_REF.2, U_HV_ERR_INT.3 (IN+)
HV_ERR_SUM: C_ERR_HF.1, R_ERR_FB.2, R_ERR_ZERO.1, U_HV_ERR_INT.2 (IN-)
HV_ERR_ZERO: C_ERR_INT.1, R_ERR_ZERO.2
HV_FB_BUF: R_ERR_FB.1, U_HV_FB_BUF.2 (IN-), U_HV_FB_BUF.6 (OUT)
HV_FB_DIV: C_DIV_BOT.1, C_DIV_HV_TOP.2 (HV_B), R_DIV_BOT.1, R_DIV_HV_TOP.2 (HV_B), U_HV_FB_BUF.3 (IN+)
HV_PROG_50: J_HV_PROG_OUT.1 (PROG), R_PROG_50R.2
HV_RTN: CHV_F1.2 (HV_B), CHV_F2.2 (HV_B), JHV_RTN_BUS.1 (HV_RTN1), JHV_RTN_BUS.2 (HV_RTN2), JHV_RTN_BUS.3 (HV_SHLD1), JHV_RTN_BUS.4 (HV_SHLD2), Q_HV_CLAMP.3 (S), Q_KCLAMP_DRV.2 (S), R_CASC_BAL_B.2 (HV_B), R_CLAMP_DUMP.2 (HV_B), R_KCLAMP_PD.2, R_QCLAMP_PD.2, R_STAR_HVRTN.2
HV_SAFE_CLAMP: J_SPI_FPGA.6 (HV_SAFE_CLAMP), U_ISO_CTRL.5 (VIC)
ISO_CLAMP_DRV: R_QCLAMP_G.1, U_INV_KCOIL.2 (A), U_ISO_CTRL.12 (VOC)
ISO_CLAMP_STAT_DIV: R_CLAMP_STAT.2, R_CLAMP_STAT_B.1, U_ISO_CTRL.11 (VID)
ISO_CLR_N: U_DAC0.14 (CLR_N), U_DAC1.14 (CLR_N), U_DAC2.14 (CLR_N), U_DAC3.14 (CLR_N), U_ISO_CTRL.13 (VOB)
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
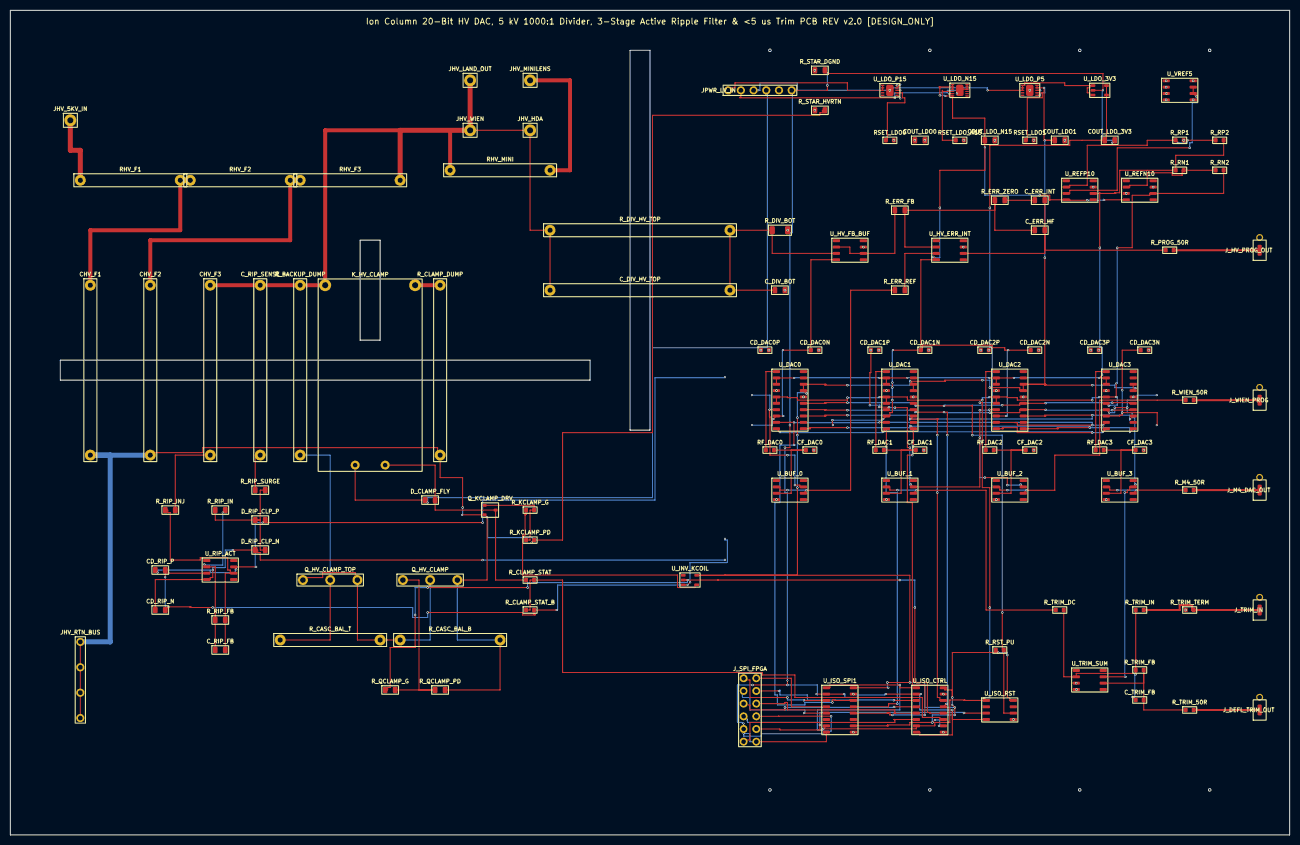
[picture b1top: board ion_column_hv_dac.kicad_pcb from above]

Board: 4 copper layers, 256.0 x 165.0 mm, 116 parts (0 on the bottom side), 77 nets.

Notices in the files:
README.md:
10. Lisans (REUSE 3.3 Uyumlu Güçlü Karşılıklı Açık Kaynak / Copyleft)
Copyright (C) 2026 berkmec (https://counfield.com/)
ikon/FPGA üretimi veya fiziksel donanım yoluyla kapatılıp tekelleştirilememesi amacıyla **`REUSE 3.3` uyumlu güçlü karşılıklı (*strongly reciprocal / copyleft*) üçlü lisans** ve çapraz-alan köprü dosyaları için **çift-copyleft (`OR`)** yapısını kullanır (ayrıntılı kapsam, `CERN-OHL-S v2` Bölüm 4 kay
